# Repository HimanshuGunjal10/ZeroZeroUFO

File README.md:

# zero zero ufo

CMPE 244 Fall 2018: [Zero Zero Ufo](http://socialledge.com/sjsu/index.php/F18:_Zero_Zero_UFO)

## Team

- Pooja Mahendra Baviskar (012535393)
- Aman Chandan (013720811)
- Himanshu Gunjal (012483341)
- Neel Patel (012468599)
- Oliver Zhu (012485707)

## Compilation and installation

Code for controller uses the `ZZU_CONTROLLER` compile mask; code for the console uses the `ZZU_CONSOLE` compile mask.
These masks can be set/unset in `sys_config.h`.

## TODO

- tunnel
- isr -> task performance
- duplicate code in GFX
- duplicate code in Obstacle, Coin

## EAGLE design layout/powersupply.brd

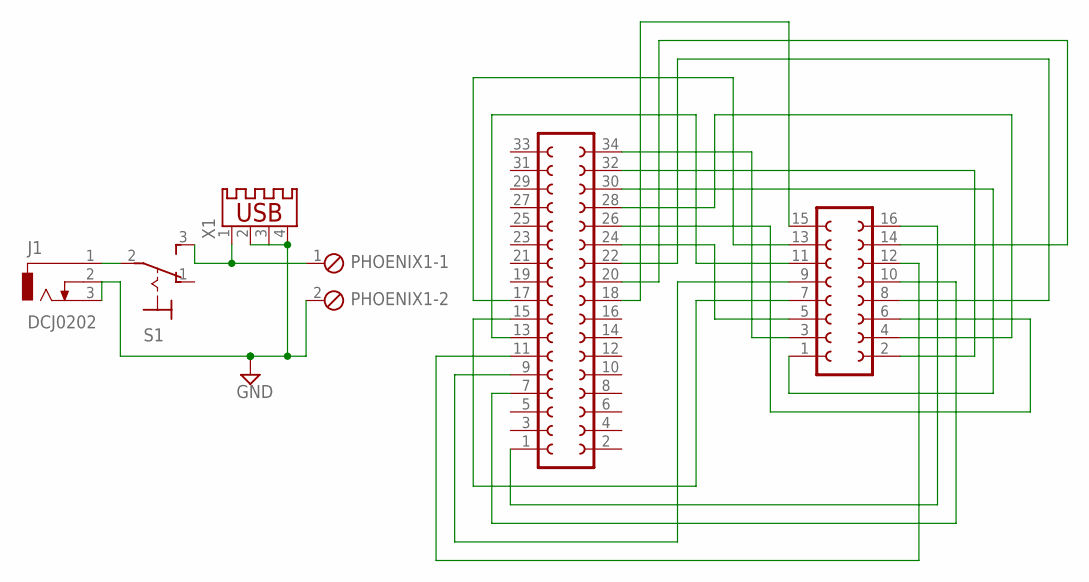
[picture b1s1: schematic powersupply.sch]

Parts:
J1: DCJ0202
PHOENIX1: MPT2; 2POL254
S1: M9040P
SV1: FE17-2
SV2: FE08-2
X1: USB-A003

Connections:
GND: J1.2, J1.3, PHOENIX1.2, X1.2, X1.3, X1.4
unnamed: J1.1, S1.2
unnamed: PHOENIX1.1, S1.3 (S), X1.1
unnamed: SV1.1, SV2.16
unnamed: SV1.7, SV2.10
unnamed: SV1.9, SV2.9
unnamed: SV1.11, SV2.12
unnamed: SV1.13, SV2.11
unnamed: SV1.15, SV2.7
unnamed: SV1.17, SV2.13
unnamed: SV1.34, SV2.3
unnamed: SV1.32, SV2.2
unnamed: SV1.30, SV2.1
unnamed: SV1.28, SV2.4
unnamed: SV1.26, SV2.6
unnamed: SV1.24, SV2.5
unnamed: SV1.22, SV2.8
unnamed: SV1.20, SV2.14
unnamed: SV1.18, SV2.15

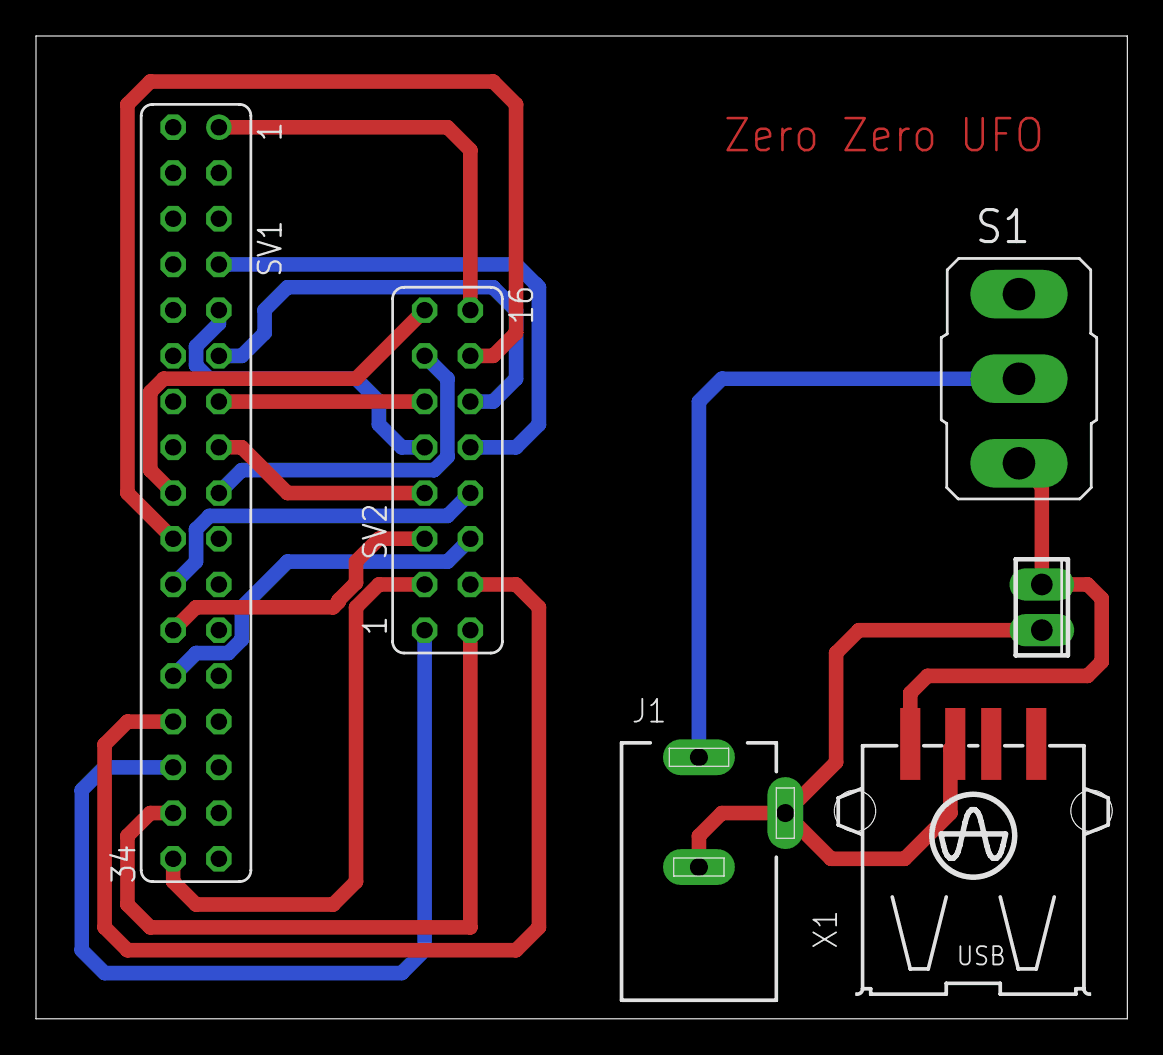
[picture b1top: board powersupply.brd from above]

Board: 2 copper layers, 60.6 x 54.6 mm, 6 parts (0 on the bottom side), 19 nets.

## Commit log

2019-05-24 adding to repo
2019-05-24 fetching from GitLab
